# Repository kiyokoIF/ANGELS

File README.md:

# ANGELS
A series of sacred musical objects to find god. 

Like Simone Weil and Rilke, I am in search of impossible beauty. For to consume is to destroy. To desire is to enforce infinite separation. Only god can cross this distance. All we can do is wait. These instruments are my prayer, my turning towards god. For there is no heaven or hell, only infinite now.

### ANGEL_001
This angel forces the user to play it with their hands held in prayer. To release pressure is to drop the object, we are forced to hold our attention `en hypomene` like Weil. The goal is to overwhelm the user with options and controls to induce a state of divine inspiration to heighten this feeling of `hypomene`.

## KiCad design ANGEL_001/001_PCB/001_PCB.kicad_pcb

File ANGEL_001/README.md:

# ANGEL_001

## Author

<!-- Insert Your Name Here -->

## Description

<!-- Describe your example here -->

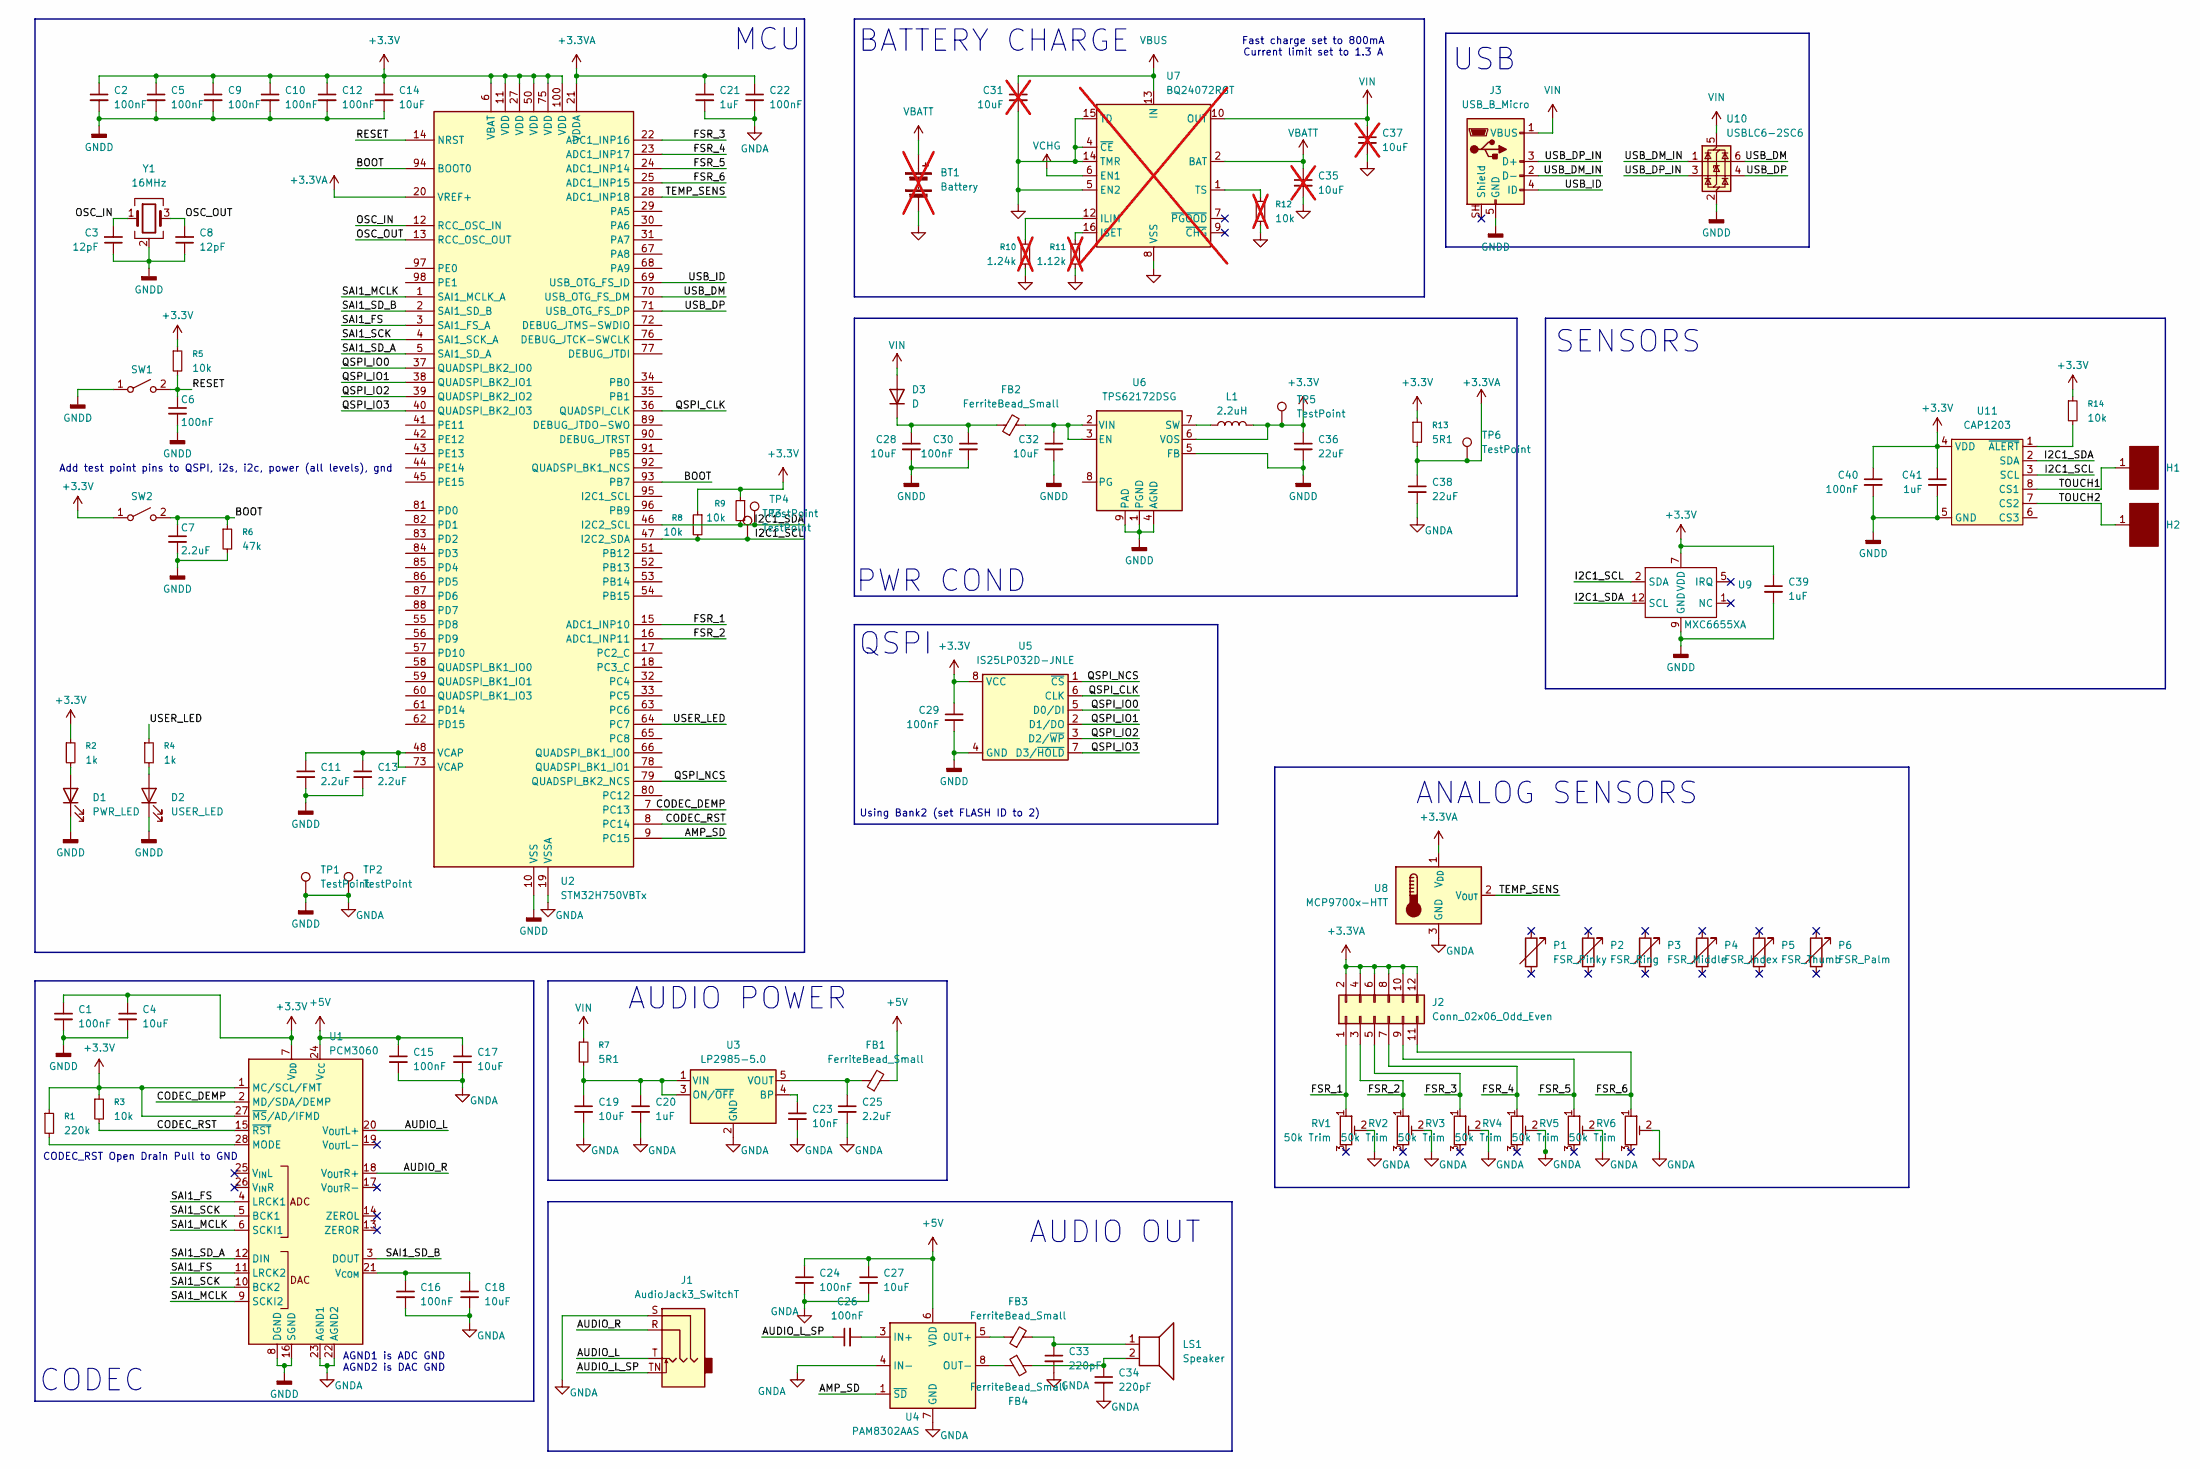
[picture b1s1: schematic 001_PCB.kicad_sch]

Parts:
BT1: Battery; JST_PH_S2B-PH-SM4-TB_1x02-1MP_P2.00mm_Horizontal; not fitted
C1, C2, C5, C6, C9, C10, C12, C15, C16, C22, C24, C26, C29, C30, C40: 100nF; C_0402_1005Metric_Pad0.74x0.62mm_HandSolder
C3, C8: 12pF; C_0402_1005Metric_Pad0.74x0.62mm_HandSolder
C4, C14, C17, C18, C19, C27, C28, C32: 10uF; C_0805_2012Metric_Pad1.18x1.45mm_HandSolder
C7, C11, C13, C25: 2.2uF; C_0603_1608Metric_Pad1.08x0.95mm_HandSolder
C20, C21, C39, C41: 1uF; C_0603_1608Metric_Pad1.08x0.95mm_HandSolder
C23: 10nF; C_0402_1005Metric_Pad0.74x0.62mm_HandSolder
C31, C35, C37: 10uF; C_0805_2012Metric_Pad1.18x1.45mm_HandSolder; not fitted
C33, C34: 220pF; C_0402_1005Metric_Pad0.74x0.62mm_HandSolder
C36, C38: 22uF; C_1206_3216Metric_Pad1.33x1.80mm_HandSolder
D1: PWR_LED; LED_0805_2012Metric_Pad1.15x1.40mm_HandSolder
D2: USER_LED; LED_0805_2012Metric_Pad1.15x1.40mm_HandSolder
D3: D; D_SOD-123
FB1, FB2, FB3, FB4: FerriteBead_Small; L_0402_1005Metric_Pad0.77x0.64mm_HandSolder
H1, H2: (no value)
J1: AudioJack3_SwitchT; Jack_3.5mm_CUI_SJ-3524-SMT_Horizontal
J2: Conn_02x06_Odd_Even; PinHeader_2x06_P2.00mm_Vertical
J3: USB_B_Micro; USB_Micro-B_Amphenol_10118193-0001LF_Horizontal
L1: 2.2uH; L_Murata_DFE201610P
LS1: Speaker; PinHeader_1x02_P2.00mm_Vertical
P1: FSR_Pinky
P2: FSR_Ring
P3: FSR_Middle
P4: FSR_Index
P5: FSR_Thumb
P6: FSR_Palm
R1: 220k; R_0402_1005Metric_Pad0.72x0.64mm_HandSolder
R2, R4: 1k; R_0402_1005Metric_Pad0.72x0.64mm_HandSolder
R3, R5, R8, R9, R14: 10k; R_0402_1005Metric_Pad0.72x0.64mm_HandSolder
R6: 47k; R_0402_1005Metric_Pad0.72x0.64mm_HandSolder
R7, R13: 5R1; R_0402_1005Metric_Pad0.72x0.64mm_HandSolder
R10: 1.24k; R_0402_1005Metric_Pad0.72x0.64mm_HandSolder; not fitted
R11: 1.12k; R_0402_1005Metric_Pad0.72x0.64mm_HandSolder; not fitted
R12: 10k; R_0402_1005Metric_Pad0.72x0.64mm_HandSolder; not fitted
RV1, RV2, RV3, RV4, RV5, RV6: 50k Trim; Potentiometer_Bourns_TC33X_Vertical
SW1, SW2: SW_Push_1P1T-SH_NO_CK_KMR2xxG
TP1, TP2, TP3, TP4, TP5, TP6: TestPoint; TestPoint_Pad_D1.0mm
U1: PCM3060; TSSOP-28_4.4x9.7mm_P0.65mm
U2: STM32H750VBTx; LQFP-100_14x14mm_P0.5mm
U3: LP2985-5.0; SOT-23-5
U4: PAM8302AAS; MSOP-8_3x3mm_P0.65mm
U5: IS25LP032D-JNLE; SO-8
U6: TPS62172DSG; WSON-8-1EP_2x2mm_P0.5mm_EP0.9x1.6mm_ThermalVias
U7: BQ24072RGT; VQFN-16-1EP_3x3mm_P0.5mm_EP1.6x1.6mm; not fitted
U8: MCP9700x-HTT; SOT-23-3
U9: MXC6655XA; LGA-12_2x2mm_P0.5mm
U10: USBLC6-2SC6; SOT-23-6
U11: CAP1203; TDFN-8-1EP_3x2mm_P0.5mm_EP1.80x1.65mm
Y1: 16MHz; Crystal_SMD_SeikoEpson_TSX3225-4Pin_3.2x2.5mm_HandSoldering

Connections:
+3.3V: C1.1, C2.1, C4.1, C5.1, C9.1, C10.1, C12.1, C14.1, C29.1, C36.1, C39.1, C40.1, C41.1, L1.2, R1.1, R2.1, R3.1, R5.1, R8.1, R9.1, R13.1, R14.1, SW2.1 (A), TP5.1 (1_1), U1.1 (MC/SCL/FMT), U1.7 (V_{DD}), U1.27 (~MS/AD/IFMD), U2.6 (VBAT), U2.11 (VDD), U2.27 (VDD), U2.50 (VDD), U2.75 (VDD), U2.100 (VDD), U5.8 (VCC), U6.6 (VOS), U9.7 (VDD), U11.4 (VDD)
+3.3VA: C21.1, C22.1, C38.1, J2.2, J2.4, J2.6, J2.8, J2.10, J2.12, R13.2, TP6.1 (1_1), U2.20 (VREF+), U2.21 (VDDA), U8.1 (V_{DD})
+5V: C15.1, C17.1, C24.1, C27.1, FB1.2, U1.24 (V_{CC}), U4.6 (VDD)
/AMP_SD: U2.9 (PC15), U4.1 (~SD)
/AUDIO_L: J1.T, U1.20 (V_{OUT}L+)
/AUDIO_L_SP: C26.1, J1.TN
/AUDIO_R: J1.R, U1.18 (V_{OUT}R+)
/BOOT: C7.1, R6.1, SW2.2 (B), U2.93 (PB7), U2.94 (BOOT0)
/CODEC_DEMP: U1.2 (MD/SDA/DEMP), U2.7 (PC13)
/CODEC_RST: R3.2, U1.15 (~RST), U2.8 (PC14)
/FSR_1: J2.1, RV1.1, U2.15 (ADC1_INP10)
/FSR_2: J2.3, RV2.1, U2.16 (ADC1_INP11)
/FSR_3: J2.5, RV3.1, U2.22 (ADC1_INP16)
/FSR_4: J2.7, RV4.1, U2.23 (ADC1_INP17)
/FSR_5: J2.9, RV5.1, U2.24 (ADC1_INP14)
/FSR_6: J2.11, RV6.1, U2.25 (ADC1_INP15)
/I2C1_SCL: R8.2, TP3.1 (1_1), U2.47 (I2C2_SDA), U9.2 (SDA), U11.3 (SCL)
/I2C1_SDA: R9.2, TP4.1 (1_1), U2.46 (I2C2_SCL), U9.12 (SCL), U11.2 (SDA)
/OSC_IN: C3.2, U2.12 (RCC_OSC_IN), Y1.1
/OSC_OUT: C8.2, U2.13 (RCC_OSC_OUT), Y1.3
/QSPI_CLK: U2.36 (QUADSPI_CLK), U5.6 (CLK)
/QSPI_IO0: U2.37 (QUADSPI_BK2_IO0), U5.5 (D0/DI)
/QSPI_IO1: U2.38 (QUADSPI_BK2_IO1), U5.2 (D1/DO)
/QSPI_IO2: U2.39 (QUADSPI_BK2_IO2), U5.3 (D2/~WP)
/QSPI_IO3: U2.40 (QUADSPI_BK2_IO3), U5.7 (D3/~HOLD)
/QSPI_NCS: U2.79 (QUADSPI_BK2_NCS), U5.1 (~CS)
/RESET: C6.1, R5.2, SW1.2 (B), U2.14 (NRST)
/SAI1_FS: U1.4 (LRCK1), U1.11 (LRCK2), U2.3 (SAI1_FS_A)
/SAI1_MCLK: U1.6 (SCKI1), U1.9 (SCKI2), U2.1 (SAI1_MCLK_A)
/SAI1_SCK: U1.5 (BCK1), U1.10 (BCK2), U2.4 (SAI1_SCK_A)
/SAI1_SD_A: U1.12 (DIN), U2.5 (SAI1_SD_A)
/SAI1_SD_B: U1.3 (DOUT), U2.2 (SAI1_SD_B)
/TEMP_SENS: U2.28 (ADC1_INP18), U8.2 (V_{OUT})
/TOUCH1: H1.1, U11.8 (CS1)
/TOUCH2: H2.1, U11.7 (CS2)
/USB_DM: U2.70 (USB_OTG_FS_DM), U10.6 (I/O1)
/USB_DM_IN: J3.2 (D-), U10.1 (I/O1)
/USB_DP: U2.71 (USB_OTG_FS_DP), U10.4 (I/O2)
/USB_DP_IN: J3.3 (D+), U10.3 (I/O2)
/USB_ID: J3.4 (ID), U2.69 (USB_OTG_FS_ID)
/USER_LED: R4.1, U2.64 (PC7)
GNDA: C1.2, C2.2, C3.1, C4.2, C5.2, C6.2, C7.2, C8.1, C9.2, C10.2, C11.2, C12.2, C13.2, C14.2, C15.2, C16.2, C17.2, C18.2, C19.2, C20.2, C21.2, C22.2, C23.2, C24.2, C25.2, C27.2, C28.2, C29.2, C30.2, C32.2, C33.2, C34.2, C36.2, C38.2, C39.2, C40.2, C41.2, D1.1 (K), D2.1 (K), J1.S, J3.5 (GND), R6.2, RV1.2, RV2.2, RV3.2, RV4.2, RV5.2, RV6.2, SW1.1 (A), TP1.1 (1_1), TP2.1 (1_1), U1.8 (DGND), U1.16 (SGND), U1.22 (AGND2), U1.23 (AGND1), U2.10 (VSS), U2.19 (VSSA), U2.26 (VSS), U2.49 (VSS), U2.74 (VSS), U2.99 (VSS), U3.2 (GND), U4.4 (IN-), U4.7 (GND), U5.4 (GND), U6.1 (PGND), U6.4 (AGND), U6.5 (FB), U6.9 (PAD), U8.3 (GND), U9.9 (GND), U10.2 (GND), U11.5 (GND), Y1.2 (G), Y1.4 (G)
unnamed: BT1.1 (+), C35.1, U7.2 (BAT), U7.3 (BAT)
unnamed: BT1.2 (-), C31.2, C35.2, C37.2, R10.2, R11.2, R12.2, U7.4 (~CE), U7.5 (EN2), U7.8 (VSS), U7.14 (TMR), U7.15 (TD), U7.17 (VSS)
unnamed: C11.1, C13.1, U2.48 (VCAP), U2.73 (VCAP)
unnamed: C31.1, U7.13 (IN)
unnamed: C33.1, FB3.2, LS1.1
unnamed: C34.1, FB4.2, LS1.2
unnamed: D1.2 (A), R2.2
unnamed: D2.2 (A), R4.2
unnamed: C28.1, C30.1, D3.1 (K), FB2.1
unnamed: R10.1, U7.12 (ILIM)
unnamed: R11.1, U7.16 (ISET)
unnamed: R12.1, U7.1 (TS)
unnamed: R1.2, U1.28 (MODE)
unnamed: C16.1, C18.1, U1.21 (V_{COM})
unnamed: C23.1, U3.4 (BP)
unnamed: C19.1, C20.1, R7.2, U3.1 (VIN), U3.3 (ON/~OFF)
unnamed: C25.1, FB1.1, U3.5 (VOUT)
unnamed: C26.2, U4.3 (IN+)
unnamed: FB3.1, U4.5 (OUT+)
unnamed: FB4.1, U4.8 (OUT-)
unnamed: C32.1, FB2.2, U6.2 (VIN), U6.3 (EN)
unnamed: L1.1, U6.7 (SW)
unnamed: R14.2, U11.1 (~ALERT)
VIN: C37.1, D3.2 (A), J3.1 (VBUS), R7.1, U7.10 (OUT), U7.11 (OUT), U10.5 (VBUS)

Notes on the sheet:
AUDIO POWER
QSPI
MCU
Add test point pins to QSPI, i2s, i2c, power (all levels), gnd
CODEC
AGND1 is ADC GND AGND2 is DAC GND
USB
BATTERY CHARGE
Using Bank2 (set FLASH ID to 2)
AUDIO OUT
PWR COND
SENSORS
CODEC_RST Open Drain Pull to GND
ANALOG SENSORS
Fast charge set to 800mA Current limit set to 1.3 A

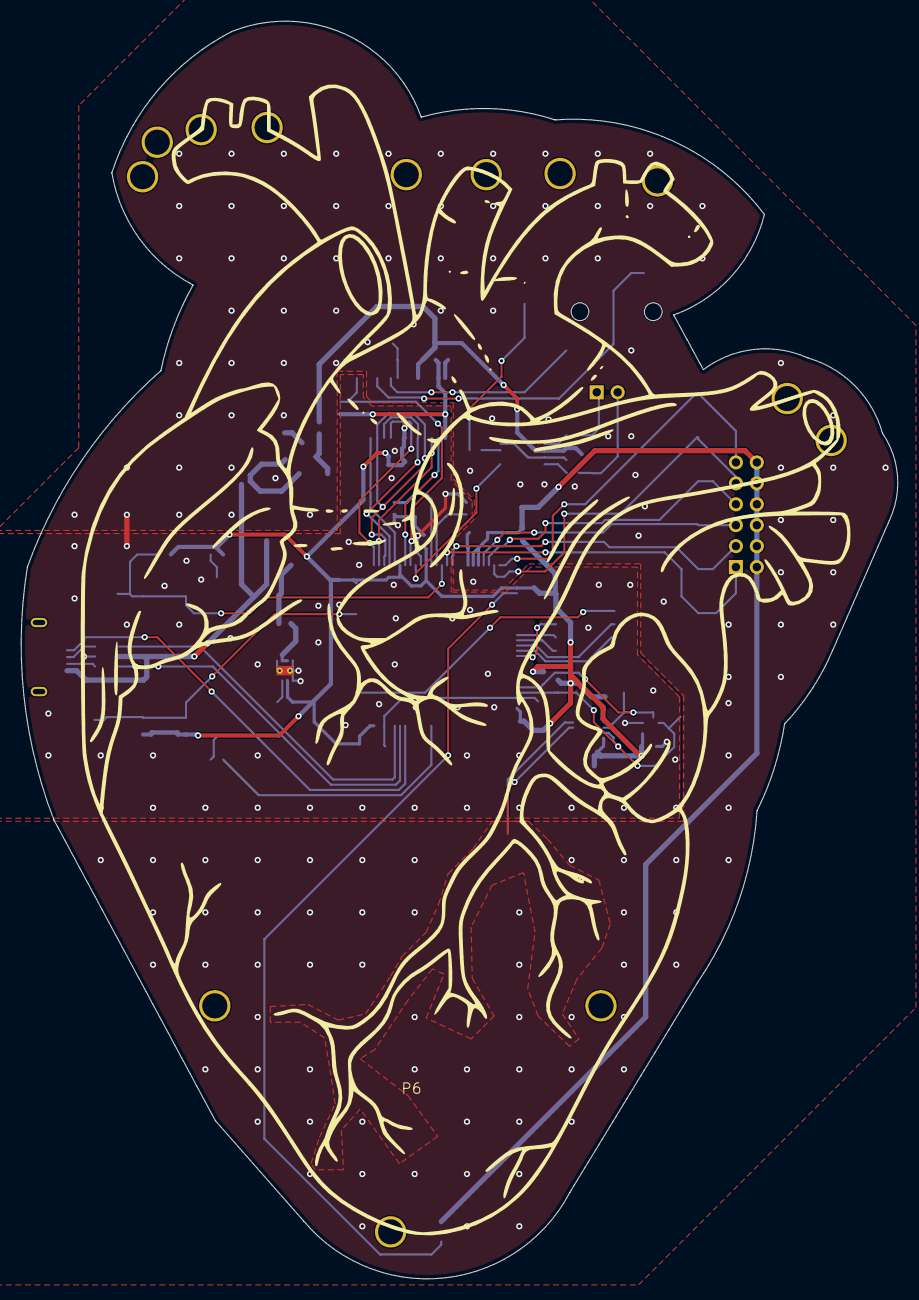
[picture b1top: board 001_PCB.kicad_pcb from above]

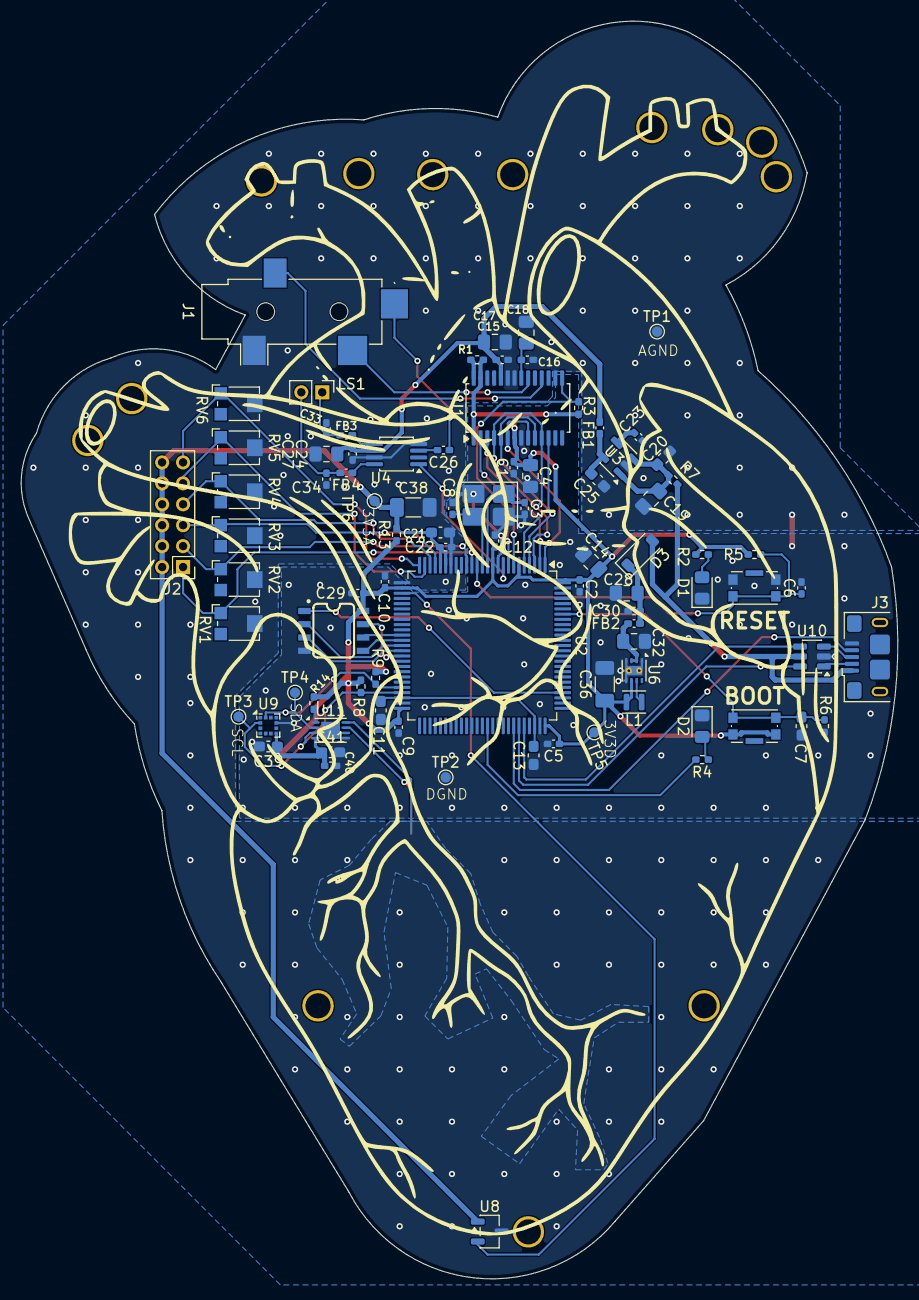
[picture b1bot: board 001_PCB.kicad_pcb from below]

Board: 2 copper layers, 83.8 x 120.2 mm, 92 parts (86 on the bottom side), 58 nets.
